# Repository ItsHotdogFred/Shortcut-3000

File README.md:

# Shortcut 3000

Shortcut 3000 is a shortcut device which solves a big problem when buying a shortcut device. If you have already brought one before you may notice that some stuff on it go unused or aren't fit for your purpose. This leads to wasted space and wasted potential. 
To avoid this happening, Shortcut 3000 contains 12 magnetic pogo pads called modules which allow you to swap stuff on it. For example: Got a key you're not using and would much rather have a rotary encoder for managing sound? Well you can do that by swapping the key module with a rotary encoder!

The secret is using i2c for communication which allows it to hold 12 modules without running out of gpio pins and also easy in code. Each module has a eeprom which is used to identify what a module is. This allows the firmware to know how to use the module. modules can also choose if they want to turn the int line into a I/O pin which is required for things like rgb strips.

| BOM Item | Footprint | Qty Needed | Source | Part / Listing | Part # / Link | Buy Qty | Unit Price | Line Total (NZD) | Shipping |
|---|---|---|---|---|---|---:|---|---:|---|
| 4.7k resistor | 0805 | 28 | LCSC | UNI-ROYAL 0805W8F4701T5E (C17673) | [Link](https://www.lcsc.com/product-detail/C17673.html) | 100 | US$0.0051 | 0.90 | Combined w/ JLC order |
| 10k resistor | 0805 | 19 | LCSC | UNI-ROYAL 0805W8F1002T5E (C17414) | [Link](https://www.lcsc.com/product-detail/C17414.html) | 100 | US$0.0034 | 0.60 | Combined w/ JLC order |
| WS2812B-2020 LED | 2.0x2.0mm | 20 | LCSC | Worldsemi WS2812B-2020-V6 (C52917434) | [Link](https://www.lcsc.com/product-detail/C52917434.html) | 20 | US$0.0921 | 3.25 | Combined w/ JLC order |
| MagneticPogo 1x05 M+F | 2.54mm | 12M+12F | Alibaba | Shenzhen Lixiang magnetic pogo 5P 2.54mm - '5p with positioning holes' | [Link](https://www.alibaba.com/product-detail/_1601788916589.html) | 12 | NZ$1.65 | 19.80 | FREE (new-buyer promo, capped NZ$36.09; normally NZ$25.59) |
| MX hotswap socket | Kailh CPG151101S11 | 5 | Owned | - | | 0 | | 0.00 | |
| 100nF cap | 0805 | 4 | LCSC | YAGEO CC0805KRX7R9BB104 (C49678) | [Link](https://www.lcsc.com/product-detail/C49678.html) | 20 | US$0.0206 | 0.73 | Combined w/ JLC order |
| 10nF cap | 0805 | 3 | LCSC | Samsung CL21B103KBANNNC (C1710) | [Link](https://www.lcsc.com/product-detail/C1710.html) | 50 | US$0.0116 | 1.02 | Combined w/ JLC order |
| 1uF cap | 0805 | 2 | LCSC | Samsung 1uF 0805 25V X7R (C116352) | [Link](https://www.lcsc.com/product-detail/C116352.html) | 10 | US$0.0409 | 0.72 | Combined w/ JLC order |
| 24LC02 EEPROM | SOIC-8 narrow | 3 | LCSC | Microchip 24LC02BT-I/SN (C5453) | [Link](https://www.lcsc.com/product-detail/C5453.html) | 5 | US$0.2957 | 2.61 | Combined w/ JLC order |
| TCA9548APWR mux | TSSOP-24 | 2 | LCSC | TI TCA9548APWR (C130026) | [Link](https://www.lcsc.com/product-detail/C130026.html) | 2 | US$0.8192 | 2.89 | Combined w/ JLC order |
| MCP23008 | DIP-18 | 1 | LCSC | Microchip MCP23008-E/P (C646745) | [Link](https://www.lcsc.com/product-detail/C646745.html) | 1 | US$2.9512 | 5.21 | Combined w/ JLC order |
| 0.66in OLED | 64x48 I2C | 1 | AliExpress | 0.66in OLED SSD1306 (Wemos shield) | [Link](https://www.aliexpress.com/item/1005010695971596.html) | 1 | NZ$5.29 | 5.29 | Choice |
| PCA9537 | TSSOP-10 | 1 | LCSC (backorder) | NXP PCA9537DP,118 (C2652305) | [Link](https://www.lcsc.com/product-detail/C2652305.html) | 1 | US$1.5903 | 2.81 | Combined w/ JLC order |
| RP2040-Zero | Castellated | 1 | AliExpress | RP2040-Zero 1PCS | [Link](https://www.aliexpress.com/item/1005010706978212.html) | 1 | NZ$5.49 | 5.49 | Choice |
| EC11E encoder | Vertical H20mm | 1 | LCSC | ALPS EC11E18244A5 (C255515) | [Link](https://www.lcsc.com/product-detail/C255515.html) | 1 | US$2.4355 | 4.30 | Combined w/ JLC order |
| Shortcut-3000 main PCB | PCB, black, 1.6mm, LeadFree HASL | 1 | JLCPCB | Shortcut-3000-Gerbers_Y11 | Y11-13394057A | 5 | US$9.50 (per 5) | 16.78 | JLC est. (shared) |
| Screen module PCB | PCB, black, 1.6mm, LeadFree HASL | 1 | JLCPCB | screen-module-Gerbers_Y10 | Y10-13394057A | 5 | US$5.20 (per 5) | 9.18 | JLC est. (shared) |
| Rotary encoder module PCB | PCB, black, 1.6mm, LeadFree HASL | 1 | JLCPCB | Rotary-encoder-module-Gerbers_Y9 | Y9-13394057A | 5 | US$5.20 (per 5) | 9.18 | JLC est. (shared) |
| RGB daisy-chain module PCB | PCB, black, 1.6mm, LeadFree HASL | 1 | JLCPCB | rgb-daisy-chain-module-Gerbers_Y8 | Y8-13394057A | 5 | US$5.20 (per 5) | 9.18 | JLC est. (shared) |
| Protoboard module PCB | PCB, black, 1.6mm, LeadFree HASL | 1 | JLCPCB | proboard-module-Gerbers_Y7 | Y7-13394057A | 5 | US$5.20 (per 5) | 9.18 | JLC est. (shared) |
| 5x MX switch module PCB | PCB, black, 1.6mm, LeadFree HASL | 1 | JLCPCB | 5-MX-Switch-Module-Gerbers_Y6 | Y6-13394057A | 5 | US$3.30 (per 5) | 5.83 | JLC est. (shared) |
| **TOTAL** | | | | | | | | **114.95** | |

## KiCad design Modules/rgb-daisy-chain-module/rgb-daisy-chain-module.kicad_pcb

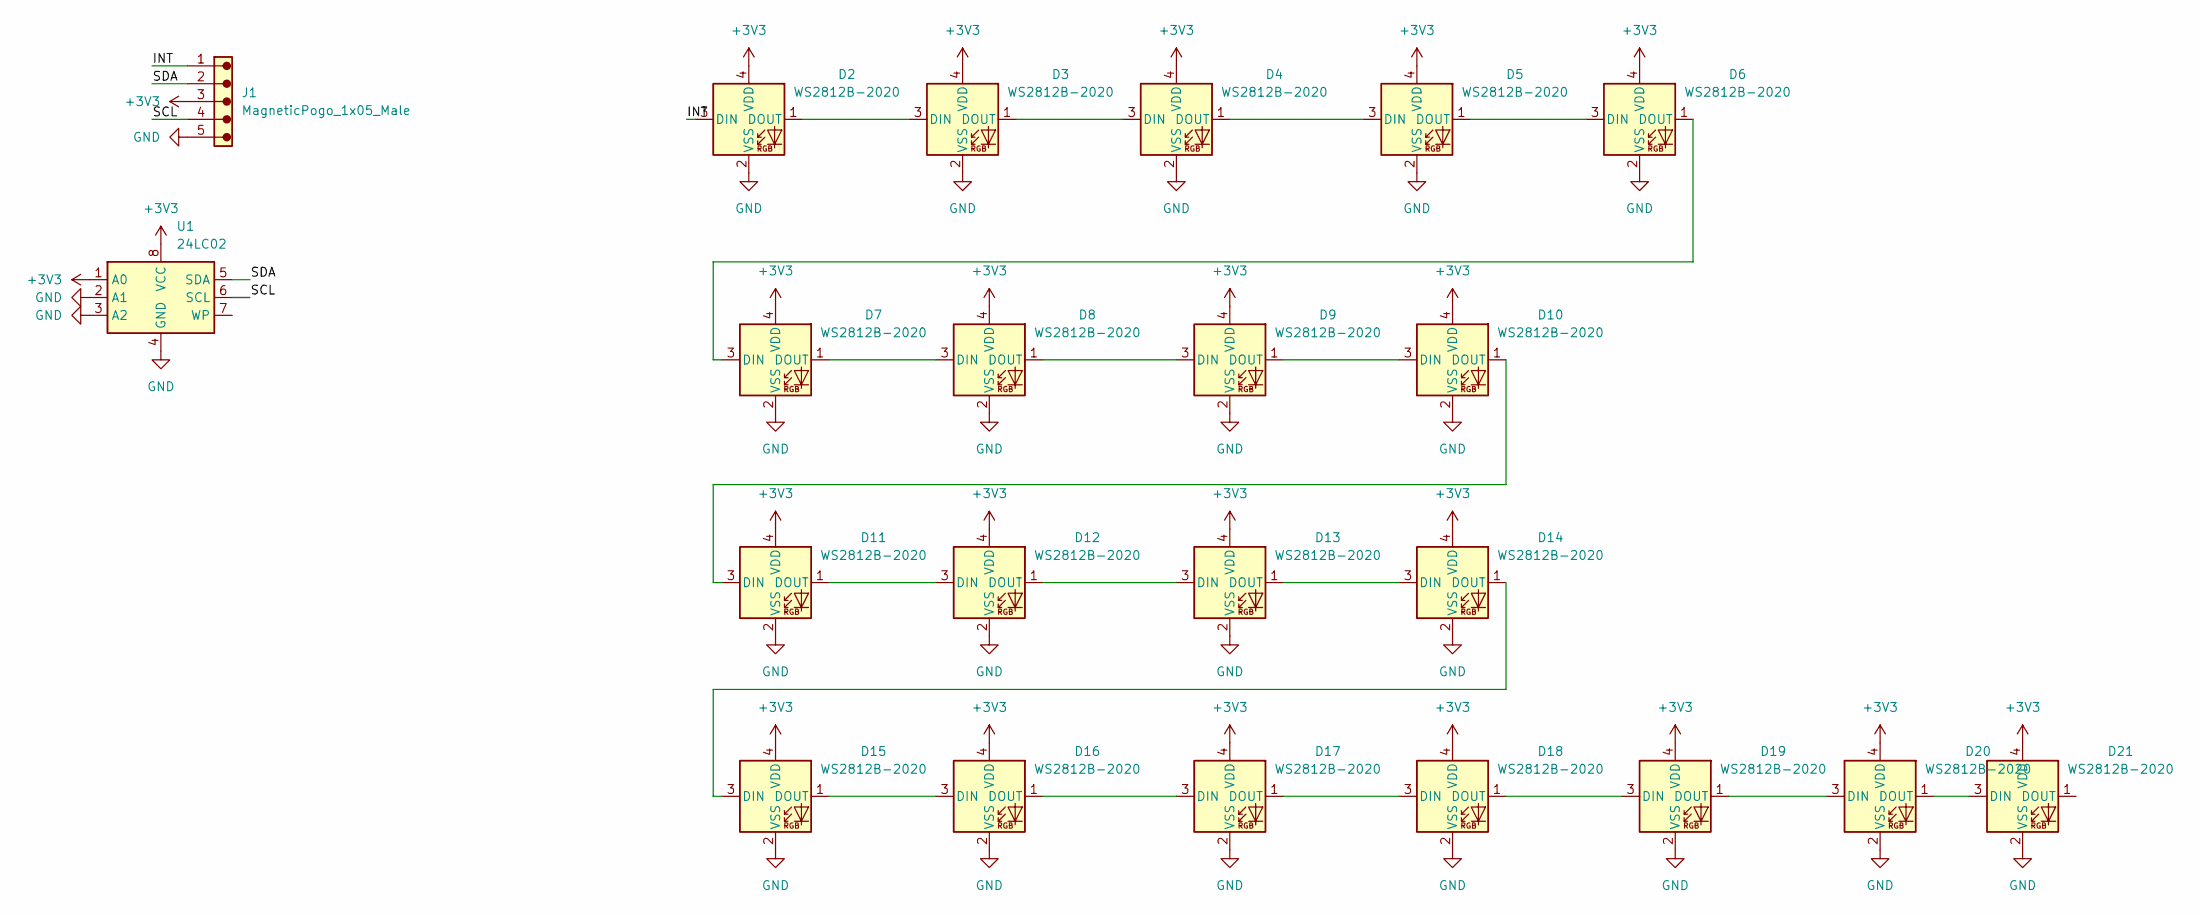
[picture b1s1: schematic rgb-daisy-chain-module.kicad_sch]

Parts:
D2, D3, D4, D5, D6, D7, D8, D9, D10, D11, D12, D13, D14, D15, D16, D17, D18, D19, D20, D21: WS2812B-2020; LED_WS2812B-2020_PLCC4_2.0x2.0mm
J1: MagneticPogo_1x05_Male; MagneticPogo_1x05_P2.54mm_Male
U1: 24LC02; JEITA_SOIC-8_3.9x4.9mm_P1.27mm

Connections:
+3V3: D2.4 (VDD), D3.4 (VDD), D4.4 (VDD), D5.4 (VDD), D6.4 (VDD), D7.4 (VDD), D8.4 (VDD), D9.4 (VDD), D10.4 (VDD), D11.4 (VDD), D12.4 (VDD), D13.4 (VDD), D14.4 (VDD), D15.4 (VDD), D16.4 (VDD), D17.4 (VDD), D18.4 (VDD), D19.4 (VDD), D20.4 (VDD), D21.4 (VDD), J1.3, U1.1 (A0), U1.8 (VCC)
/INT: D2.3 (DIN), J1.1
/SCL: J1.4, U1.6 (SCL)
/SDA: J1.2, U1.5 (SDA)
GND: D2.2 (VSS), D3.2 (VSS), D4.2 (VSS), D5.2 (VSS), D6.2 (VSS), D7.2 (VSS), D8.2 (VSS), D9.2 (VSS), D10.2 (VSS), D11.2 (VSS), D12.2 (VSS), D13.2 (VSS), D14.2 (VSS), D15.2 (VSS), D16.2 (VSS), D17.2 (VSS), D18.2 (VSS), D19.2 (VSS), D20.2 (VSS), D21.2 (VSS), J1.5, U1.2 (A1), U1.3 (A2), U1.4 (GND)
unnamed: D2.1 (DOUT), D3.3 (DIN)
unnamed: D3.1 (DOUT), D4.3 (DIN)
unnamed: D4.1 (DOUT), D5.3 (DIN)
unnamed: D5.1 (DOUT), D6.3 (DIN)
unnamed: D6.1 (DOUT), D7.3 (DIN)
unnamed: D7.1 (DOUT), D8.3 (DIN)
unnamed: D8.1 (DOUT), D9.3 (DIN)
unnamed: D9.1 (DOUT), D10.3 (DIN)
unnamed: D10.1 (DOUT), D11.3 (DIN)
unnamed: D11.1 (DOUT), D12.3 (DIN)
unnamed: D12.1 (DOUT), D13.3 (DIN)
unnamed: D13.1 (DOUT), D14.3 (DIN)
unnamed: D14.1 (DOUT), D15.3 (DIN)
unnamed: D15.1 (DOUT), D16.3 (DIN)
unnamed: D16.1 (DOUT), D17.3 (DIN)
unnamed: D17.1 (DOUT), D18.3 (DIN)
unnamed: D18.1 (DOUT), D19.3 (DIN)
unnamed: D19.1 (DOUT), D20.3 (DIN)
unnamed: D20.1 (DOUT), D21.3 (DIN)

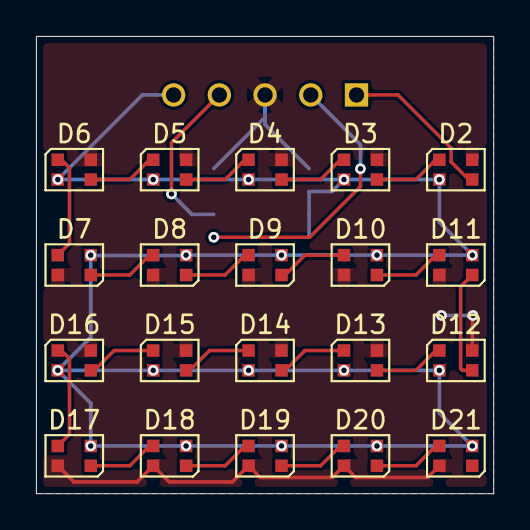
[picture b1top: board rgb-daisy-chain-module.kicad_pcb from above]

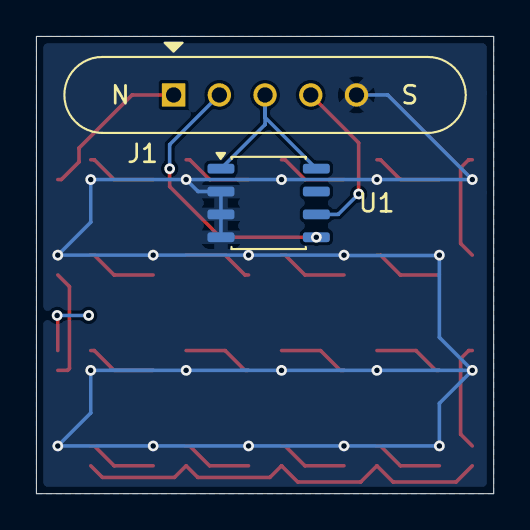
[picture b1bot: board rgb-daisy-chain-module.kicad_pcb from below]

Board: 2 copper layers, 25.4 x 25.4 mm, 22 parts (2 on the bottom side), 24 nets.

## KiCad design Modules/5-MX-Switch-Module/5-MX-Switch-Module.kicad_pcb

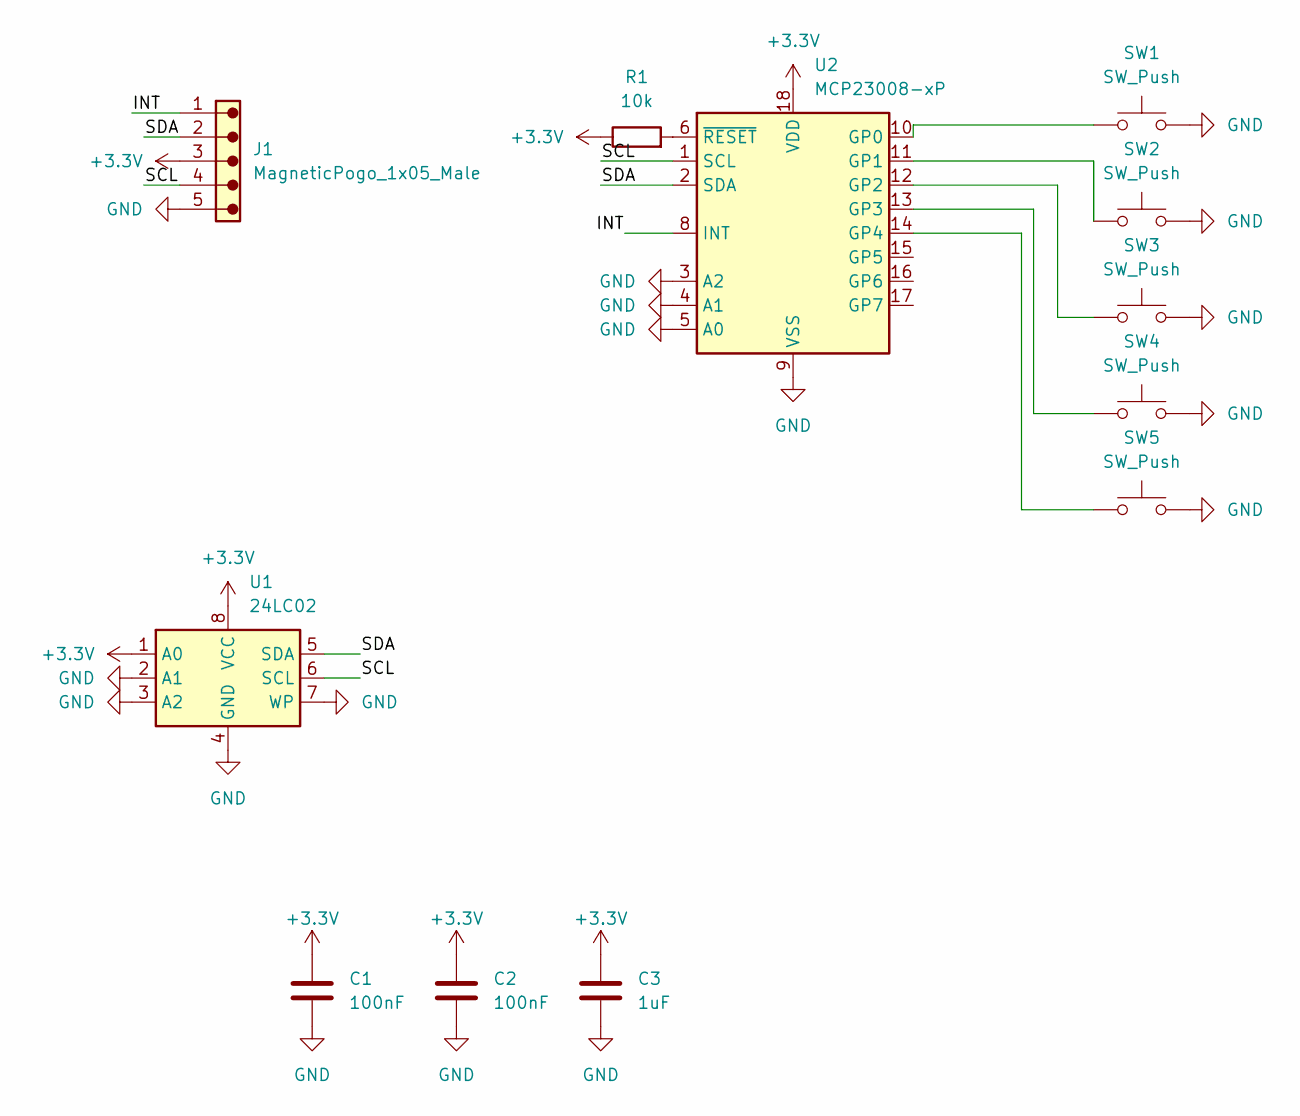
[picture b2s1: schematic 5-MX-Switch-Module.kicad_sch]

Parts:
C1, C2: 100nF; C_0805_2012Metric
C3: 1uF; C_0805_2012Metric
J1: MagneticPogo_1x05_Male; MagneticPogo_1x05_P2.54mm_Male
R1: 10k; R_0815_2038Metric
SW1, SW2, SW3, SW4, SW5: SW_Push; SW_MX_HS_S_CPG151101S11_1u
U1: 24LC02; SOIC-8_3.9x4.9mm_P1.27mm
U2: MCP23008-xP; DIP-18_W7.62mm_SMDSocket_SmallPads

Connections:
+3.3V: C1.1, C2.1, C3.1, J1.3, R1.1, U1.1 (A0), U1.8 (VCC), U2.18 (VDD)
/INT: J1.1, U2.8 (INT)
/SCL: J1.4, U1.6 (SCL), U2.1 (SCL)
/SDA: J1.2, U1.5 (SDA), U2.2 (SDA)
GND: C1.2, C2.2, C3.2, J1.5, SW1.2, SW2.2, SW3.2, SW4.2, SW5.2, U1.2 (A1), U1.3 (A2), U1.4 (GND), U1.7 (WP), U2.3 (A2), U2.4 (A1), U2.5 (A0), U2.9 (VSS)
unnamed: SW1.1, U2.10 (GP0)
unnamed: SW2.1, U2.11 (GP1)
unnamed: SW3.1, U2.12 (GP2)
unnamed: SW4.1, U2.13 (GP3)
unnamed: SW5.1, U2.14 (GP4)
unnamed: R1.2, U2.6 (~RESET)

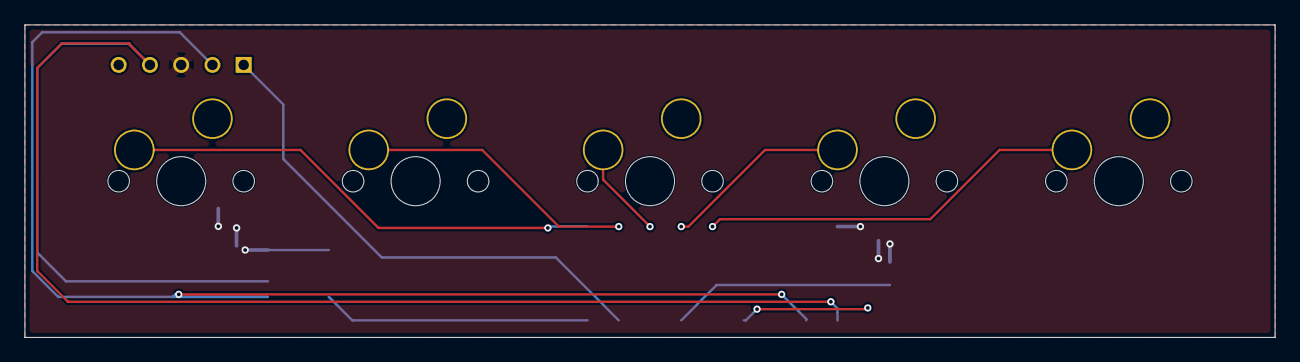
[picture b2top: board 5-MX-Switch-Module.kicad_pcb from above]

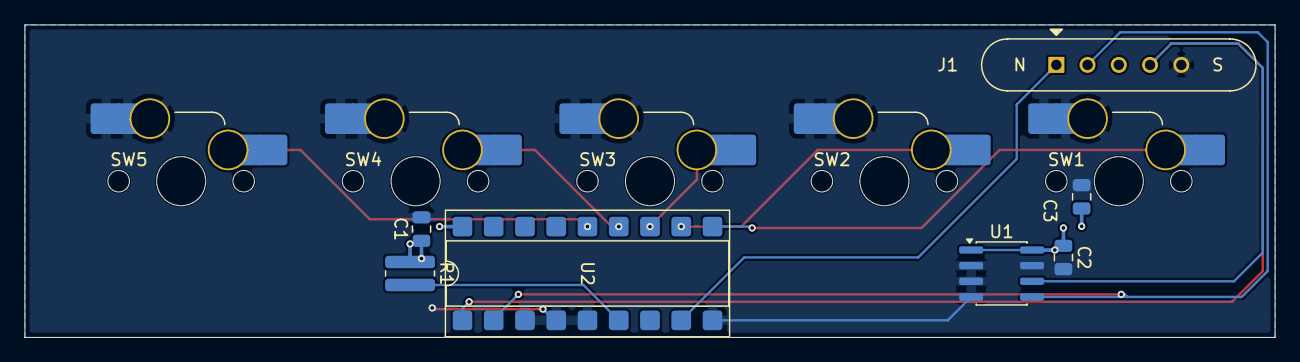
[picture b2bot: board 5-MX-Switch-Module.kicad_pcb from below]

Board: 2 copper layers, 101.6 x 25.4 mm, 12 parts (12 on the bottom side), 11 nets.

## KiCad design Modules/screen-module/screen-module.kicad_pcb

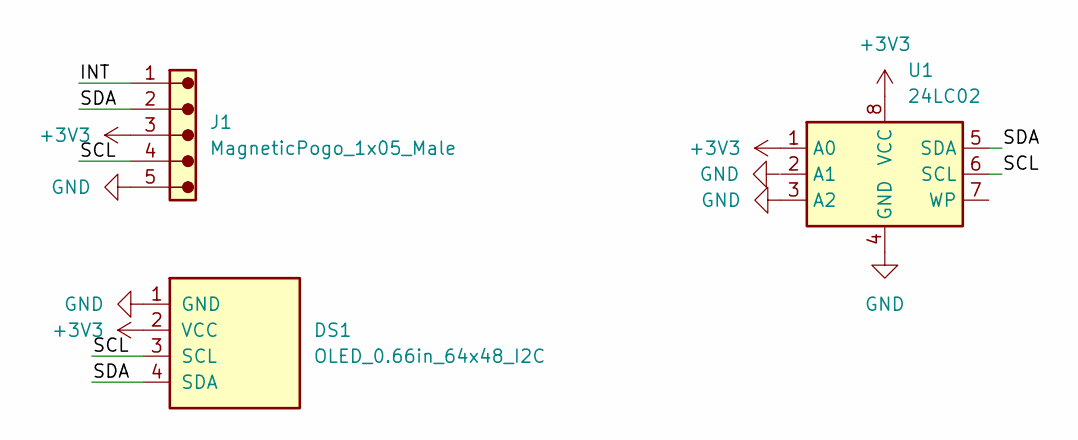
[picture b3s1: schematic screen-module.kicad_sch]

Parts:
DS1: OLED_0.66in_64x48_I2C; OLED_0.66in_64x48_I2C_REA006448A
J1: MagneticPogo_1x05_Male; MagneticPogo_1x05_P2.54mm_Male
U1: 24LC02; SOIC-8_3.9x4.9mm_P1.27mm

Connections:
+3V3: DS1.2 (VCC), J1.3, U1.1 (A0), U1.8 (VCC)
/INT: J1.1
/SCL: DS1.3 (SCL), J1.4, U1.6 (SCL)
/SDA: DS1.4 (SDA), J1.2, U1.5 (SDA)
GND: DS1.1 (GND), J1.5, U1.3 (A2), U1.4 (GND)

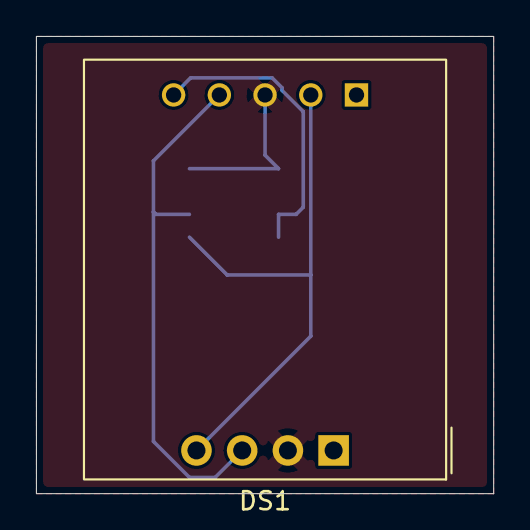
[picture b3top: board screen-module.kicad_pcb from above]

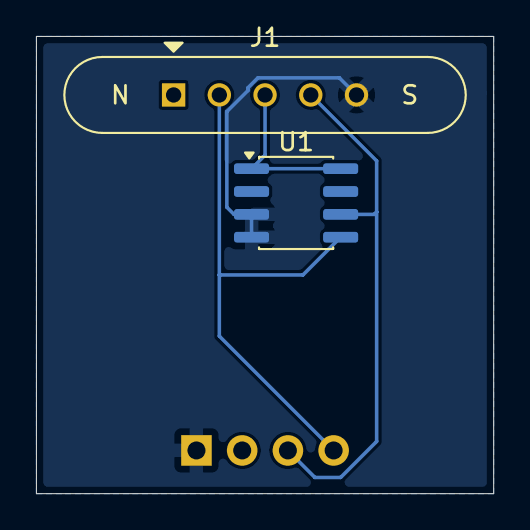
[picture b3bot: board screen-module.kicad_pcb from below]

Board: 2 copper layers, 25.4 x 25.4 mm, 3 parts (2 on the bottom side), 4 nets.

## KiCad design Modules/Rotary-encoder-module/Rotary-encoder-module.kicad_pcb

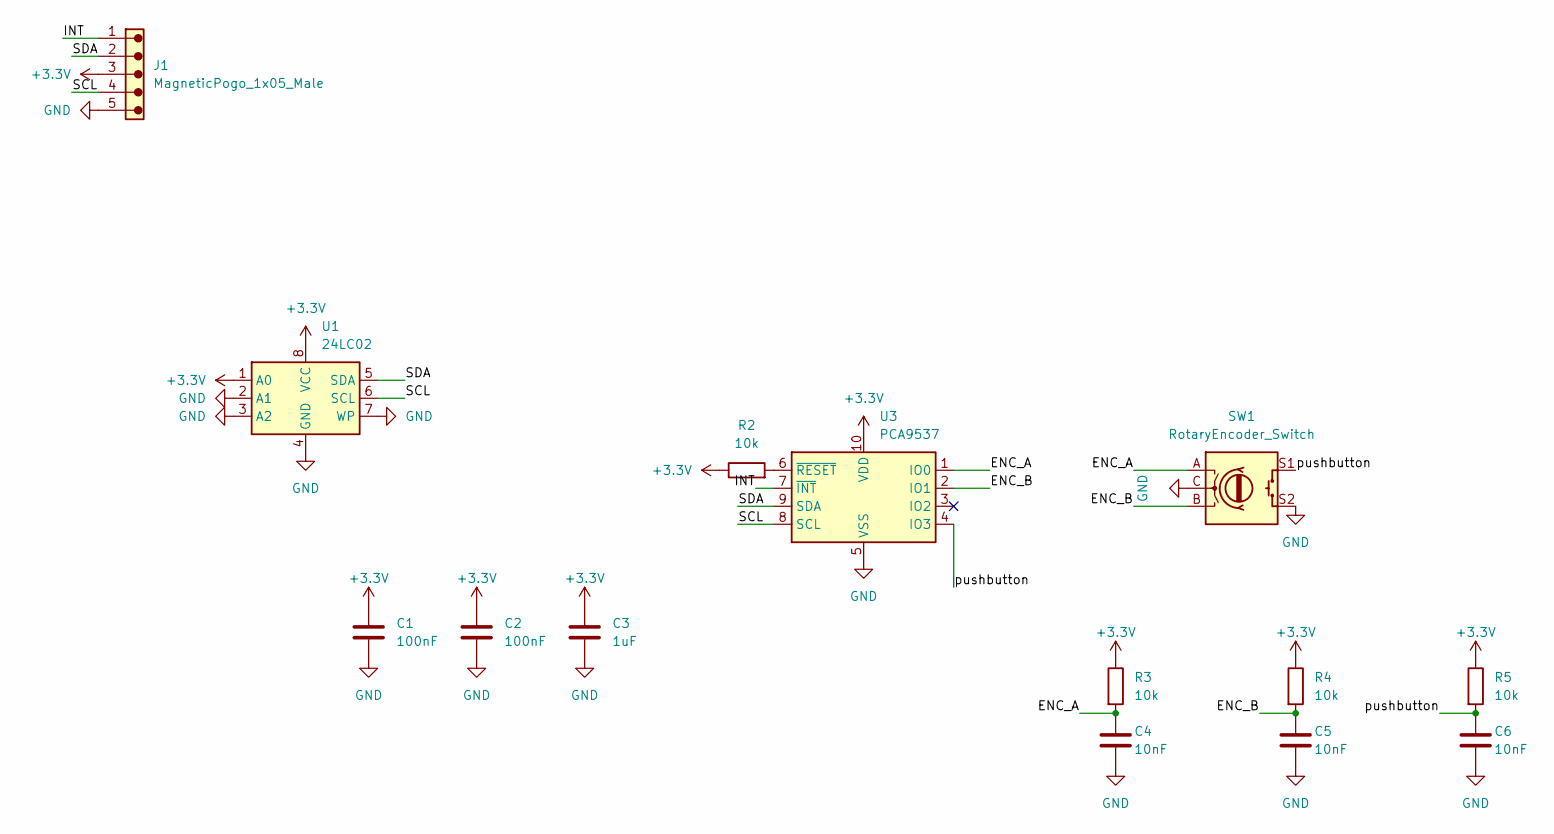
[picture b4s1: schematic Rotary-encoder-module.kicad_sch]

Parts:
C1, C2: 100nF; C_0805_2012Metric
C3: 1uF; C_0805_2012Metric
C4, C5, C6: 10nF; C_0805_2012Metric
J1: MagneticPogo_1x05_Male; MagneticPogo_1x05_P2.54mm_Male
R2: 10k; R_0815_2038Metric
R3, R4, R5: 10k; R_0805_2012Metric
SW1: RotaryEncoder_Switch; RotaryEncoder_Alps_EC11E-Switch_Vertical_H20mm
U1: 24LC02; SOIC-8_3.9x4.9mm_P1.27mm
U3: PCA9537; TSSOP-10_3x3mm_P0.5mm

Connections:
+3.3V: C1.1, C2.1, C3.1, J1.3, R2.1, R3.1, R4.1, R5.1, U1.1 (A0), U1.8 (VCC), U3.10 (VDD)
/ENC_A: C4.1, R3.2, SW1.A, U3.1 (IO0)
/ENC_B: C5.1, R4.2, SW1.B, U3.2 (IO1)
/INT: J1.1, U3.7 (~INT)
/SCL: J1.4, U1.6 (SCL), U3.8 (SCL)
/SDA: J1.2, U1.5 (SDA), U3.9 (SDA)
/pushbutton: C6.1, R5.2, SW1.S1, U3.4 (IO3)
GND: C1.2, C2.2, C3.2, C4.2, C5.2, C6.2, J1.5, SW1.C, SW1.S2, U1.2 (A1), U1.3 (A2), U1.4 (GND), U1.7 (WP), U3.5 (VSS)
unnamed: R2.2, U3.6 (~RESET)

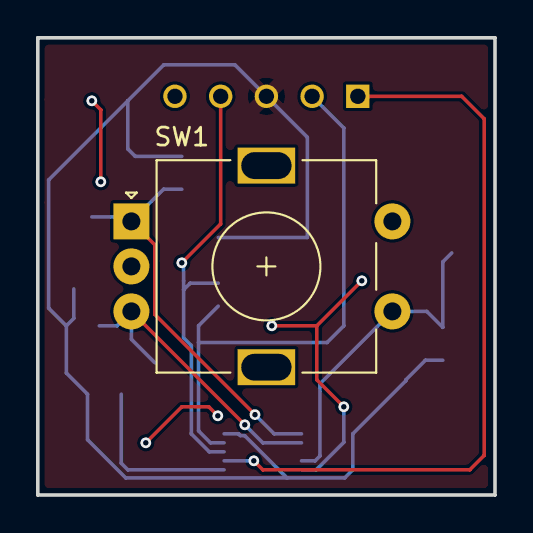
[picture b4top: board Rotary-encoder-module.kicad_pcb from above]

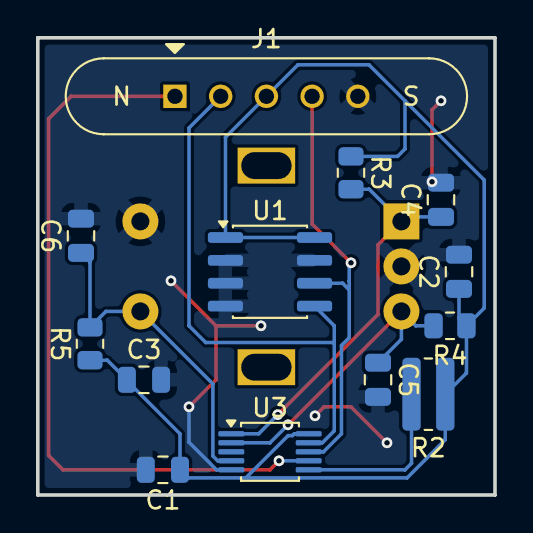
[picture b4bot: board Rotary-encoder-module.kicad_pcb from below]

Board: 2 copper layers, 25.4 x 25.4 mm, 14 parts (13 on the bottom side), 9 nets.

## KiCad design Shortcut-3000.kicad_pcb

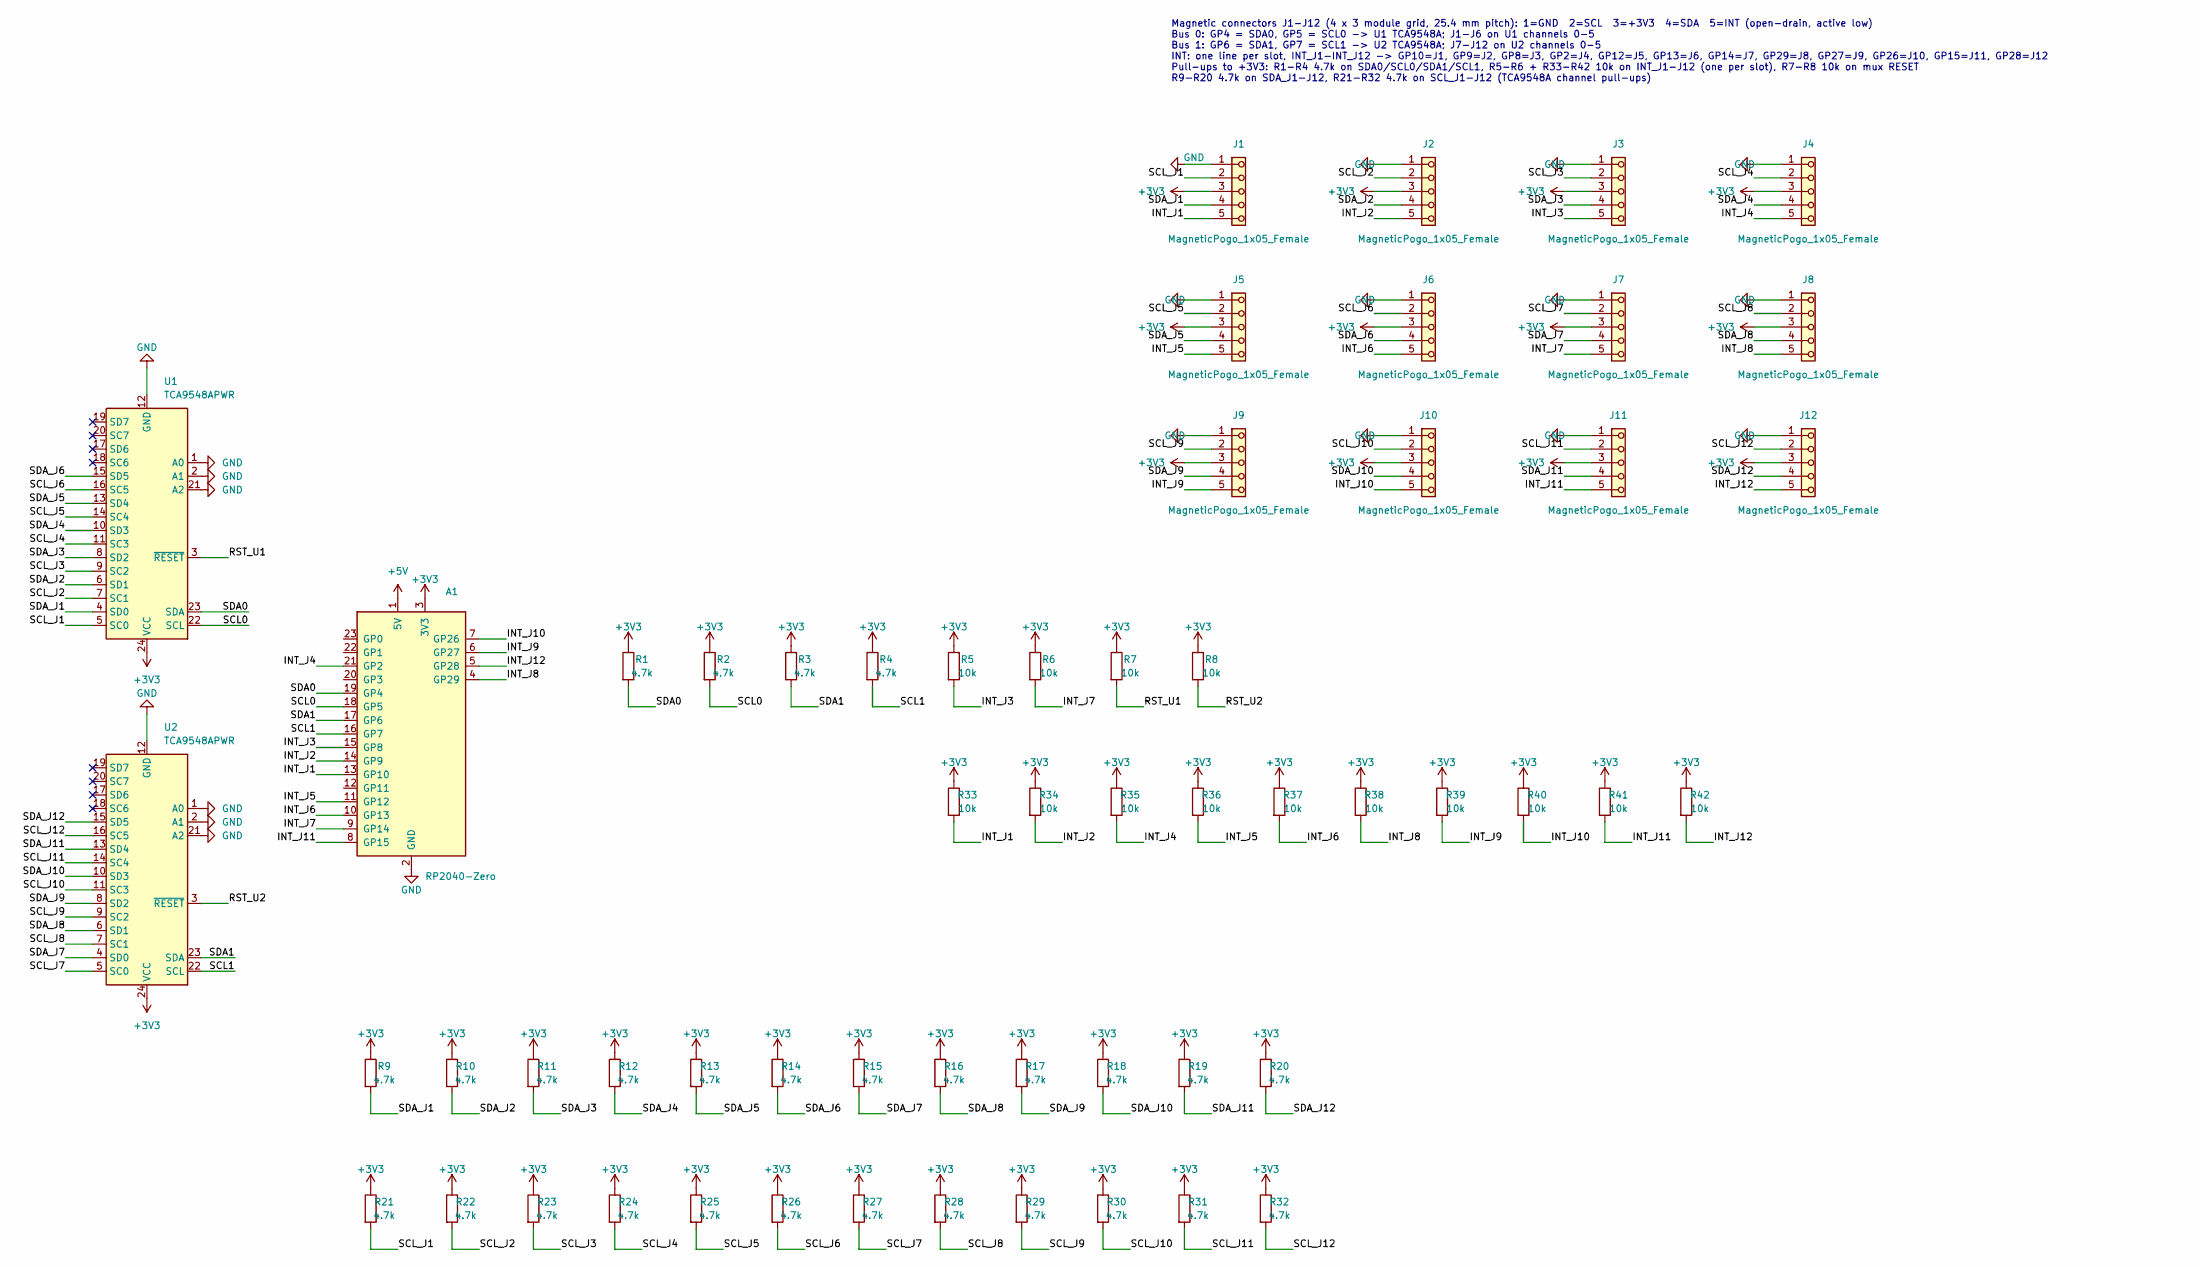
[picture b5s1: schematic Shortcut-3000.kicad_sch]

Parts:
A1: RP2040-Zero; RP2040-Zero_Castellated
J1, J2, J3, J4, J5, J6, J7, J8, J9, J10, J11, J12: MagneticPogo_1x05_Female; MagneticPogo_1x05_P2.54mm_Female
R1, R2, R3, R4, R9, R10, R11, R12, R13, R14, R15, R16, R17, R18, R19, R20, R21, R22, R23, R24, R25, R26, R27, R28, R29, R30, R31, R32: 4.7k; R_0805_2012Metric
R5, R6, R7, R8, R33, R34, R35, R36, R37, R38, R39, R40, R41, R42: 10k; R_0805_2012Metric
U1, U2: TCA9548APWR; TSSOP-24_4.4x7.8mm_P0.65mm

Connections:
+3V3: A1.3 (3V3), J1.3, J2.3, J3.3, J4.3, J5.3, J6.3, J7.3, J8.3, J9.3, J10.3, J11.3, J12.3, R1.1, R2.1, R3.1, R4.1, R5.1, R6.1, R7.1, R8.1, R9.1, R10.1, R11.1, R12.1, R13.1, R14.1, R15.1, R16.1, R17.1, R18.1, R19.1, R20.1, R21.1, R22.1, R23.1, R24.1, R25.1, R26.1, R27.1, R28.1, R29.1, R30.1, R31.1, R32.1, R33.1, R34.1, R35.1, R36.1, R37.1, R38.1, R39.1, R40.1, R41.1, R42.1, U1.24 (VCC), U2.24 (VCC)
+5V: A1.1 (5V)
/INT_J1: A1.13 (GP10), J1.5, R33.2
/INT_J2: A1.14 (GP9), J2.5, R34.2
/INT_J3: A1.15 (GP8), J3.5, R5.2
/INT_J4: A1.21 (GP2), J4.5, R35.2
/INT_J5: A1.11 (GP12), J5.5, R36.2
/INT_J6: A1.10 (GP13), J6.5, R37.2
/INT_J7: A1.9 (GP14), J7.5, R6.2
/INT_J8: A1.4 (GP29), J8.5, R38.2
/INT_J9: A1.6 (GP27), J9.5, R39.2
/INT_J10: A1.7 (GP26), J10.5, R40.2
/INT_J11: A1.8 (GP15), J11.5, R41.2
/INT_J12: A1.5 (GP28), J12.5, R42.2
/RST_U1: R7.2, U1.3 (~RESET)
/RST_U2: R8.2, U2.3 (~RESET)
/SCL0: A1.18 (GP5), R2.2, U1.22 (SCL)
/SCL1: A1.16 (GP7), R4.2, U2.22 (SCL)
/SCL_J1: J1.2, R21.2, U1.5 (SC0)
/SCL_J2: J2.2, R22.2, U1.7 (SC1)
/SCL_J3: J3.2, R23.2, U1.9 (SC2)
/SCL_J4: J4.2, R24.2, U1.11 (SC3)
/SCL_J5: J5.2, R25.2, U1.14 (SC4)
/SCL_J6: J6.2, R26.2, U1.16 (SC5)
/SCL_J7: J7.2, R27.2, U2.5 (SC0)
/SCL_J8: J8.2, R28.2, U2.7 (SC1)
/SCL_J9: J9.2, R29.2, U2.9 (SC2)
/SCL_J10: J10.2, R30.2, U2.11 (SC3)
/SCL_J11: J11.2, R31.2, U2.14 (SC4)
/SCL_J12: J12.2, R32.2, U2.16 (SC5)
/SDA0: A1.19 (GP4), R1.2, U1.23 (SDA)
/SDA1: A1.17 (GP6), R3.2, U2.23 (SDA)
/SDA_J1: J1.4, R9.2, U1.4 (SD0)
/SDA_J2: J2.4, R10.2, U1.6 (SD1)
/SDA_J3: J3.4, R11.2, U1.8 (SD2)
/SDA_J4: J4.4, R12.2, U1.10 (SD3)
/SDA_J5: J5.4, R13.2, U1.13 (SD4)
/SDA_J6: J6.4, R14.2, U1.15 (SD5)
/SDA_J7: J7.4, R15.2, U2.4 (SD0)
/SDA_J8: J8.4, R16.2, U2.6 (SD1)
/SDA_J9: J9.4, R17.2, U2.8 (SD2)
/SDA_J10: J10.4, R18.2, U2.10 (SD3)
/SDA_J11: J11.4, R19.2, U2.13 (SD4)
/SDA_J12: J12.4, R20.2, U2.15 (SD5)
GND: A1.2 (GND), J1.1, J2.1, J3.1, J4.1, J5.1, J6.1, J7.1, J8.1, J9.1, J10.1, J11.1, J12.1, U1.1 (A0), U1.2 (A1), U1.12 (GND), U1.21 (A2), U2.1 (A0), U2.2 (A1), U2.12 (GND), U2.21 (A2)

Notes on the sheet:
Magnetic connectors J1-J12 (4 x 3 module grid, 25.4 mm pitch): 1=GND 2=SCL 3=+3V3 4=SDA 5=INT (open-drain, active low) Bus 0: GP4 = SDA0, GP5 = SCL0 -> U1 TCA9548A; J1-J6 on U1 channels 0-5 Bus 1: GP6 = SDA1, GP7 = SCL1 -> U2 TCA9548A; J7-J12 on U2 channels 0-5 INT: one line per slot, INT_J1-INT_J1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

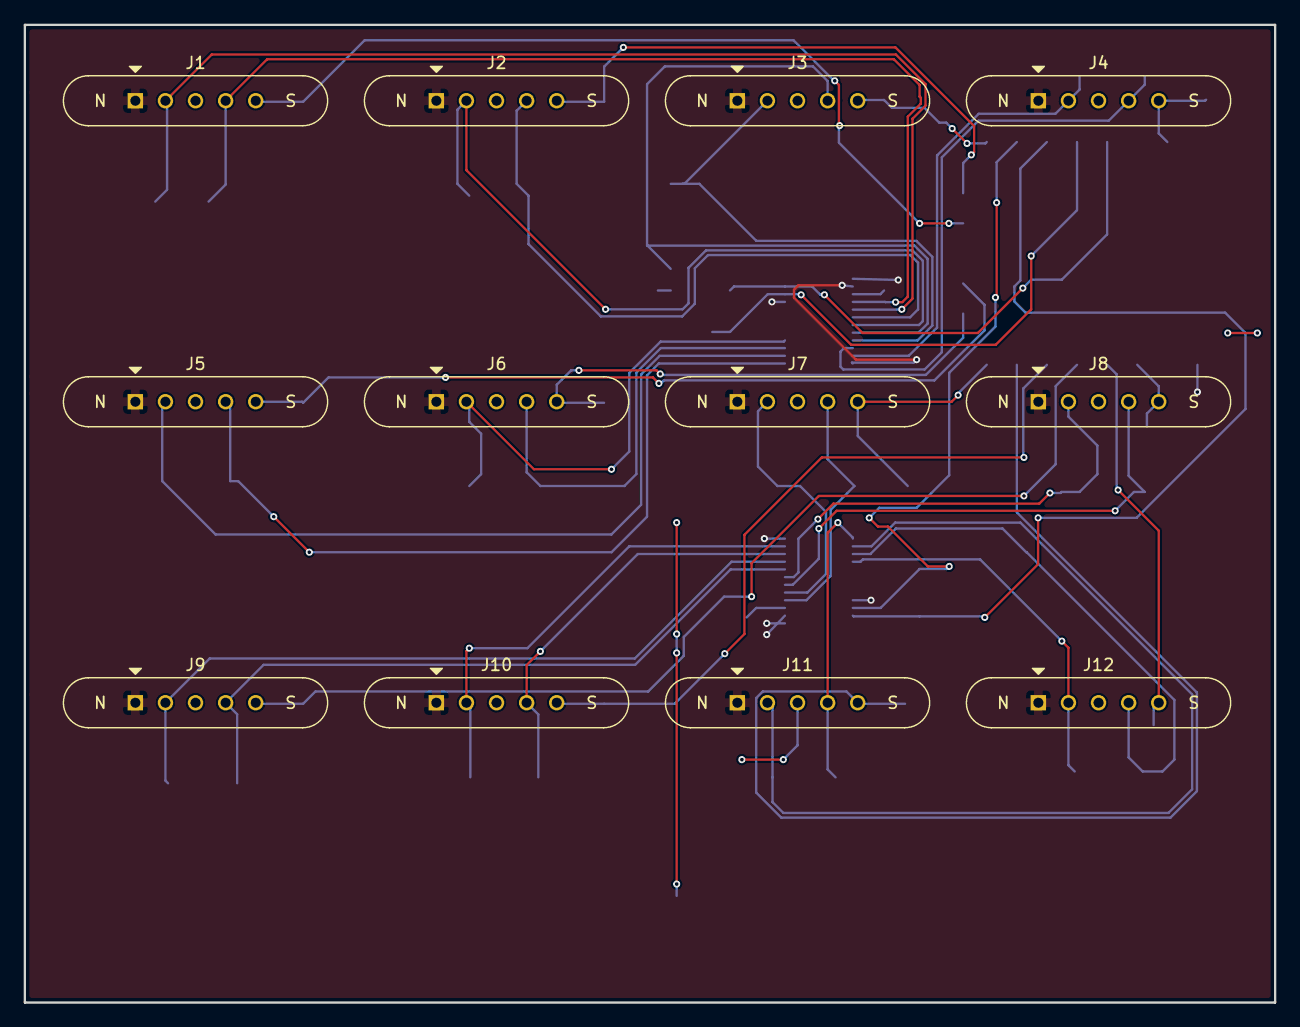
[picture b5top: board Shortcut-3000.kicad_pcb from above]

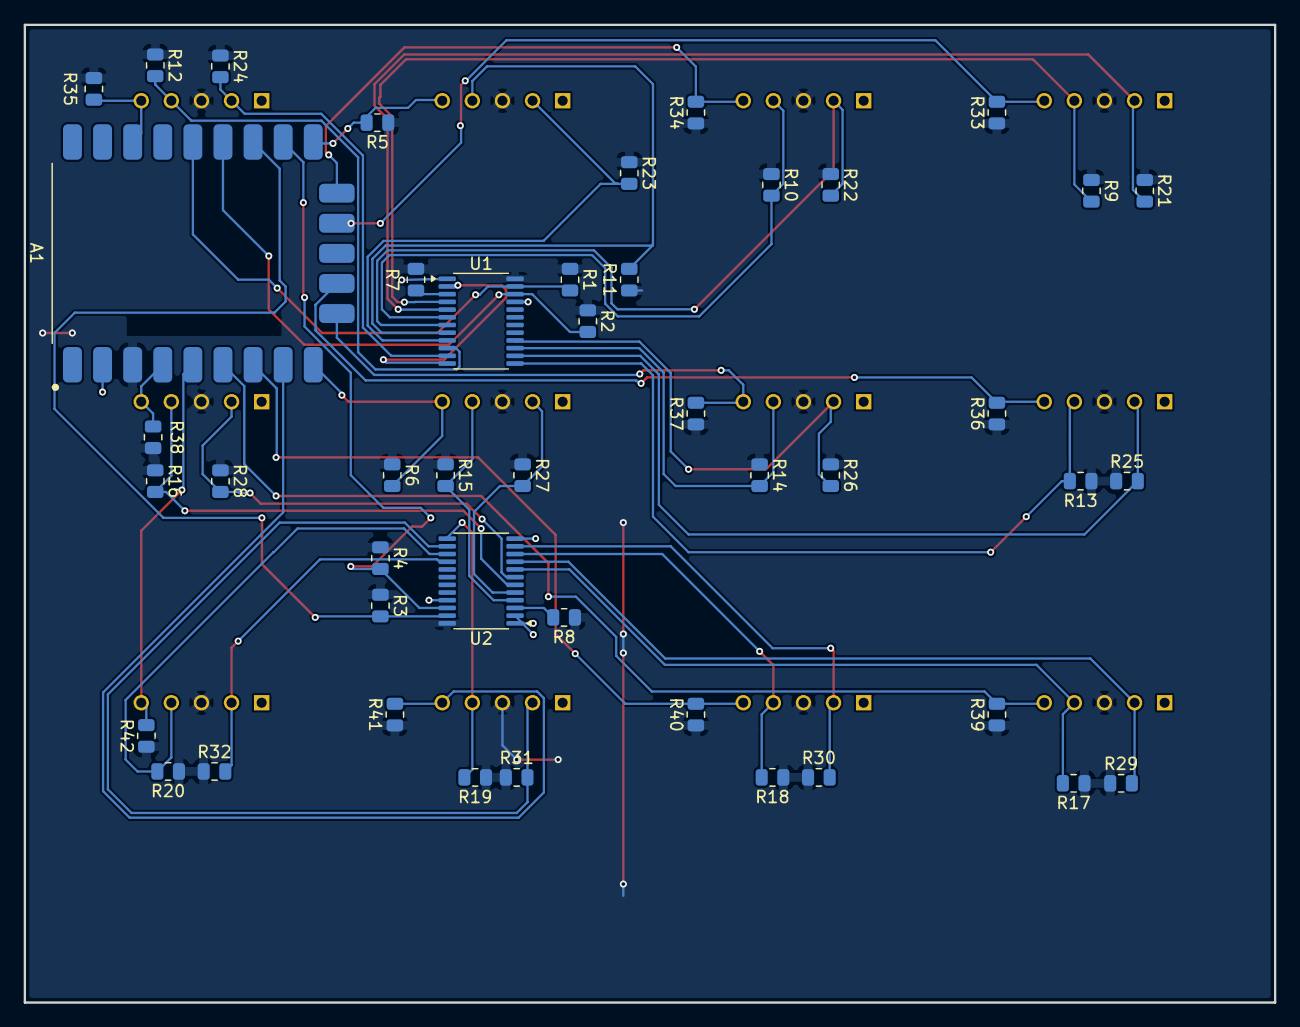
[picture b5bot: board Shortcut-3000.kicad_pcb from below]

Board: 2 copper layers, 105.5 x 82.5 mm, 57 parts (45 on the bottom side), 44 nets.
